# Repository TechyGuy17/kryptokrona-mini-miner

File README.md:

** THE HARDWARE IS CURRENTLY NOT TESTED **

# Kryptokrona mini miner
A bare minimum miner with a Cortex-A53 Allwinner H616 SoC made with KiCad

## Overview
A simple as possible SBC for mining kryptokrona (XKR), based on [Kononenko-K's h616 devboard](https://github.com/Kononenko-K/Allwinner_H616_Devboard/)

## [Hardware](Hardware)

The board features 64-bit 1.5GHz Quad-Core Cortex-A53 Allwinner H616 SOC, up to 8 Gbit (1 GB) of FBGA-96 16x DDR3 RAM, Micro SD slot, USB HS Host connector and integrated CP2102 USB-UART converter. 4 layers; 3,5/3,5 mil; 0,35/0,15 via, 80u prepreg.
There are [KiCad project](/Hardware), [Gerber files](/Hardware/gerber) and [PDF](/Hardware/output.pdf) avaliable.

## Software
** NOT TESTED SOFTWARE, IT COMPILES BUT MIGHT NOT ACTUALLY WORK ** 
Due to the switch to the more accessable AXP313a, the project is no longer fully compatible with the Orange Pi zero 2- But there is a workaround!

For this guide we will be using armbian, since its lightweight and has support for our processor.

The recommended OS to run this in is Ubuntu 22.04

start by downloading this repo to get the necessary files

```git clone https://github.com/TechyGuy17/kryptokrona-mini-miner```

After that we want to download the "Armbian Builder"

```git clone https://github.com/armbian/build && cd build```

Now we will do a dry run of the builder to let it download all the sources and also fix the file structure

```./compile.sh build BOARD=orangepizero2 BRANCH=current BUILD_DESKTOP=no BUILD_MINIMAL=yes KERNEL_CONFIGURE=no RELEASE=bookworm```

Now we are ready to start doing the patching. If you havent moved around the folders you can use theese commands to do the whole process

```mkdir userpatches/kernel/archive/sunxi-6.6```

```cp ../kryptokrona-mini-miner/Patches/updated-tp-axp313a.patch userpatches/kernel/archive/sunxi-6.6 ```

```cp ../kryptokrona-mini-miner/Patches/updated-tp-axp313a-uboot.patch userpatches/u-boot/u-boot-sunxi```

What this does is move in a few files that make it so we switch out everything regarding the AXP305 to 313a

Now we are ready to build for real!

```./compile.sh build BOARD=orangepizero2 BRANCH=current BUILD_DESKTOP=no BUILD_MINIMAL=yes KERNEL_CONFIGURE=no RELEASE=bookworm```

After this, you should have an image ready to be flashed to a SD card and then ready to be booted! Plug in an wifi/ethernet adapter in the board and a USB-c cable from your computer to the miner and then it should light up! The board will show up as a serial device and can be accessed through software like puTTY or minicom. settings are 115200,8,1 meaning 115200 baud rate, 8 bits and one stop bit.

# Bonus
If you want XKRig (XMRig) preinstalled to your keep on reading!

Run the following command to move the required script to the right folder 
```mv ../kryptokrona-mini-miner/Patches/customize-image.sh userpatches```

When this is in place, rerun the compile 

```./compile.sh build BOARD=orangepizero2 BRANCH=current BUILD_DESKTOP=no BUILD_MINIMAL=yes KERNEL_CONFIGURE=no RELEASE=bookworm```

This will go a lot faster since most the code is cached by now

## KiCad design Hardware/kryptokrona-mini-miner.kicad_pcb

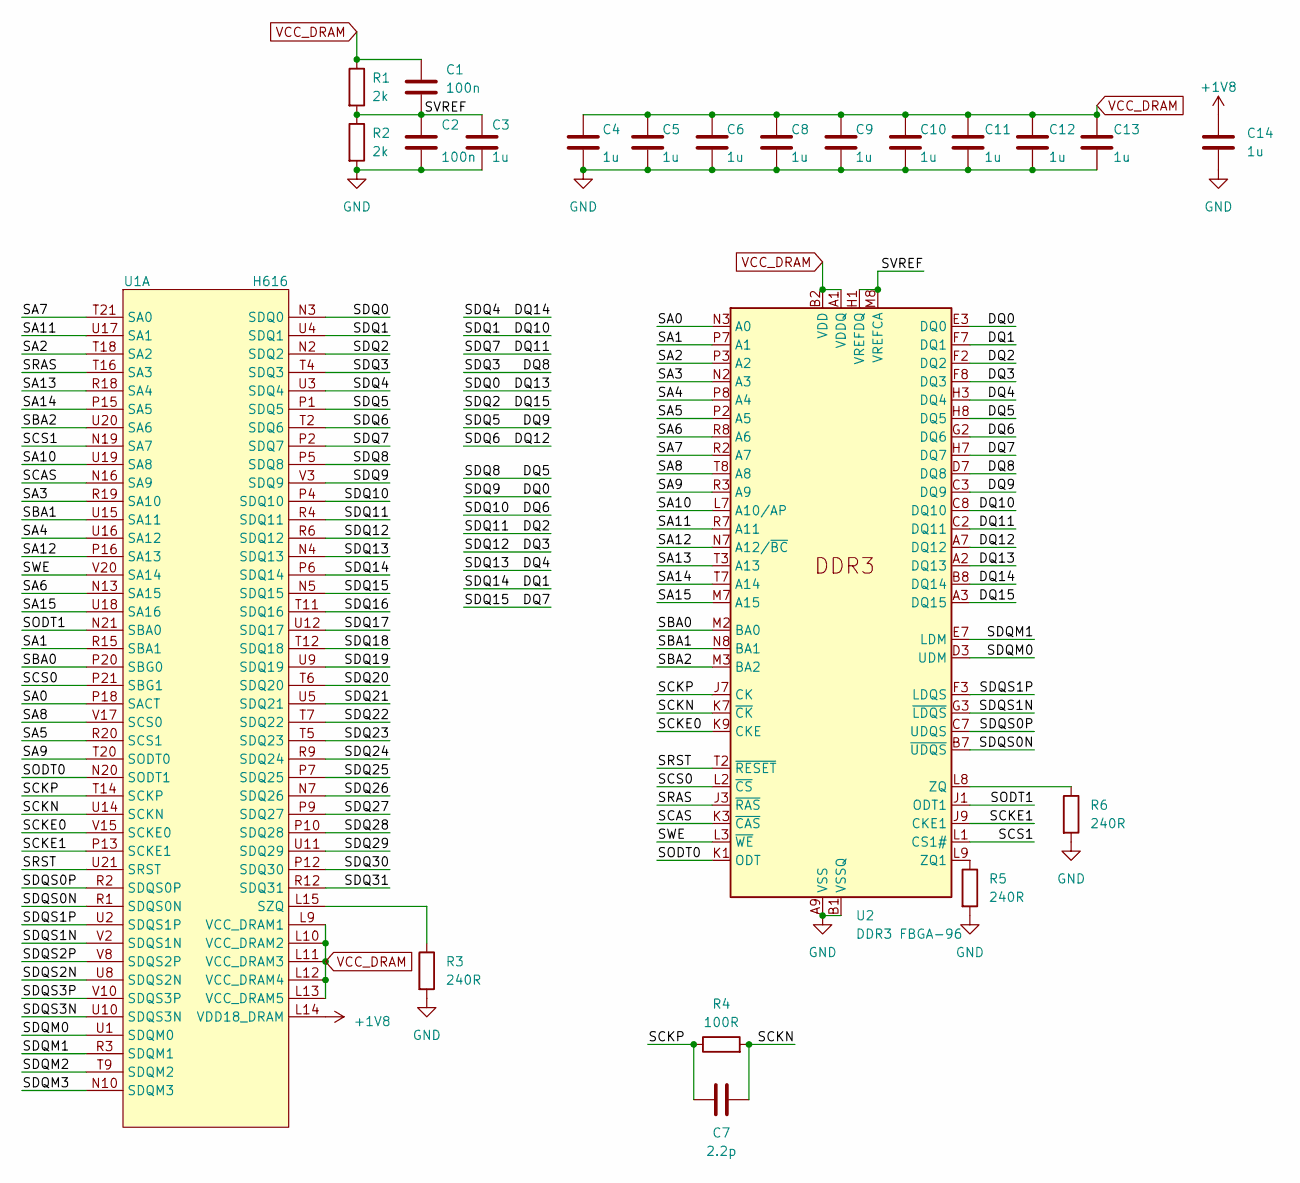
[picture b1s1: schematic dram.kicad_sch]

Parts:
C1, C2: 100n; C_0402_1005Metric_Pad0.74x0.62mm_HandSolder
C3, C4, C5, C6, C8, C9, C10, C11, C12, C13, C14: 1u; C_0402_1005Metric_Pad0.74x0.62mm_HandSolder
C7: 2.2p; C_0402_1005Metric_Pad0.74x0.62mm_HandSolder
R1, R2: 2k; R_0402_1005Metric_Pad0.72x0.64mm_HandSolder
R3, R5, R6: 240R; R_0402_1005Metric_Pad0.72x0.64mm_HandSolder
R4: 100R; R_0402_1005Metric_Pad0.72x0.64mm_HandSolder
U1: H616; H616_TFBGA284
U2: DDR3 FBGA-96; BGA-96_9.0x13.0mm_Layout2x3x16_P0.8mm

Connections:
+1V8: C14.1, U1.L14 (VDD18_DRAM); also elsewhere on the board
/DRAM/DQ0: U1.V3 (SDQ9), U2.E3 (DQ0)
/DRAM/DQ1: U1.P6 (SDQ14), U2.F7 (DQ1)
/DRAM/DQ2: U1.R4 (SDQ11), U2.F2 (DQ2)
/DRAM/DQ3: U1.R6 (SDQ12), U2.F8 (DQ3)
/DRAM/DQ4: U1.N4 (SDQ13), U2.H3 (DQ4)
/DRAM/DQ5: U1.P5 (SDQ8), U2.H8 (DQ5)
/DRAM/DQ6: U1.P4 (SDQ10), U2.G2 (DQ6)
/DRAM/DQ7: U1.N5 (SDQ15), U2.H7 (DQ7)
/DRAM/DQ8: U1.T4 (SDQ3), U2.D7 (DQ8)
/DRAM/DQ9: U1.P1 (SDQ5), U2.C3 (DQ9)
/DRAM/DQ10: U1.U4 (SDQ1), U2.C8 (DQ10)
/DRAM/DQ11: U1.P2 (SDQ7), U2.C2 (DQ11)
/DRAM/DQ12: U1.T2 (SDQ6), U2.A7 (DQ12)
/DRAM/DQ13: U1.N3 (SDQ0), U2.A2 (DQ13)
/DRAM/DQ14: U1.U3 (SDQ4), U2.B8 (DQ14)
/DRAM/DQ15: U1.N2 (SDQ2), U2.A3 (DQ15)
/DRAM/SA0: U1.P18 (SACT), U2.N3 (A0)
/DRAM/SA1: U1.R15 (SBA1), U2.P7 (A1)
/DRAM/SA2: U1.T18 (SA2), U2.P3 (A2)
/DRAM/SA3: U1.R19 (SA10), U2.N2 (A3)
/DRAM/SA4: U1.U16 (SA12), U2.P8 (A4)
/DRAM/SA5: U1.R20 (SCS1), U2.P2 (A5)
/DRAM/SA6: U1.N13 (SA15), U2.R8 (A6)
/DRAM/SA7: U1.T21 (SA0), U2.R2 (A7)
/DRAM/SA8: U1.V17 (SCS0), U2.T8 (A8)
/DRAM/SA9: U1.T20 (SODT0), U2.R3 (A9)
/DRAM/SA10: U1.U19 (SA8), U2.L7 (A10/AP)
/DRAM/SA11: U1.U17 (SA1), U2.R7 (A11)
/DRAM/SA12: U1.P16 (SA13), U2.N7 (A12/~BC)
/DRAM/SA13: U1.R18 (SA4), U2.T3 (A13)
/DRAM/SA14: U1.P15 (SA5), U2.T7 (A14)
/DRAM/SA15: U1.U18 (SA16), U2.M7 (A15)
/DRAM/SBA0: U1.P20 (SBG0), U2.M2 (BA0)
/DRAM/SBA1: U1.U15 (SA11), U2.N8 (BA1)
/DRAM/SBA2: U1.U20 (SA6), U2.M3 (BA2)
/DRAM/SCAS: U1.N16 (SA9), U2.K3 (~CAS)
/DRAM/SCKE0: U1.V15 (SCKE0), U2.K9 (CKE)
/DRAM/SCKE1: U1.P13 (SCKE1), U2.J9 (CKE1)
/DRAM/SCKN: C7.2, R4.2, U1.U14 (SCKN), U2.K7 (~CK)
/DRAM/SCKP: C7.1, R4.1, U1.T14 (SCKP), U2.J7 (CK)
/DRAM/SCS0: U1.P21 (SBG1), U2.L2 (~CS)
/DRAM/SCS1: U1.N19 (SA7), U2.L1 (CS1#)
/DRAM/SDQ16: U1.T11 (SDQ16)
/DRAM/SDQ17: U1.U12 (SDQ17)
/DRAM/SDQ18: U1.T12 (SDQ18)
/DRAM/SDQ19: U1.U9 (SDQ19)
/DRAM/SDQ20: U1.T6 (SDQ20)
/DRAM/SDQ21: U1.U5 (SDQ21)
/DRAM/SDQ22: U1.T7 (SDQ22)
/DRAM/SDQ23: U1.T5 (SDQ23)
/DRAM/SDQ24: U1.R9 (SDQ24)
/DRAM/SDQ25: U1.P7 (SDQ25)
/DRAM/SDQ26: U1.N7 (SDQ26)
/DRAM/SDQ27: U1.P9 (SDQ27)
/DRAM/SDQ28: U1.P10 (SDQ28)
/DRAM/SDQ29: U1.U11 (SDQ29)
/DRAM/SDQ30: U1.P12 (SDQ30)
/DRAM/SDQ31: U1.R12 (SDQ31)
/DRAM/SDQM0: U1.U1 (SDQM0), U2.D3 (UDM)
/DRAM/SDQM1: U1.R3 (SDQM1), U2.E7 (LDM)
/DRAM/SDQM2: U1.T9 (SDQM2)
/DRAM/SDQM3: U1.N10 (SDQM3)
/DRAM/SDQS0N: U1.R1 (SDQS0N), U2.B7 (~UDQS)
/DRAM/SDQS0P: U1.R2 (SDQS0P), U2.C7 (UDQS)
/DRAM/SDQS1N: U1.V2 (SDQS1N), U2.G3 (~LDQS)
/DRAM/SDQS1P: U1.U2 (SDQS1P), U2.F3 (LDQS)
/DRAM/SDQS2N: U1.U8 (SDQS2N)
/DRAM/SDQS2P: U1.V8 (SDQS2P)
/DRAM/SDQS3N: U1.U10 (SDQS3N)
/DRAM/SDQS3P: U1.V10 (SDQS3P)
/DRAM/SODT0: U1.N20 (SODT1), U2.K1 (ODT)
/DRAM/SODT1: U1.N21 (SBA0), U2.J1 (ODT1)
/DRAM/SRAS: U1.T16 (SA3), U2.J3 (~RAS)
/DRAM/SRST: U1.U21 (SRST), U2.T2 (~RESET)
/DRAM/SVREF: C1.2, C2.1, C3.1, R1.2, R2.1, U2.H1 (VREFDQ), U2.M8 (VREFCA)
/DRAM/SWE: U1.V20 (SA14), U2.L3 (~WE)
GND: C2.2, C3.2, C4.2, C5.2, C6.2, C8.2, C9.2, C10.2, C11.2, C12.2, C13.2, C14.2, R2.2, R3.2, R5.2, R6.2, U2.A9 (VSS), U2.B1 (VSSQ), U2.B3 (VSS), U2.B9 (VSSQ), U2.D1 (VSSQ), U2.D8 (VSSQ), U2.E1 (VSS), U2.E2 (VSSQ), U2.E8 (VSSQ), U2.F9 (VSSQ), U2.G1 (VSSQ), U2.G8 (VSS), U2.G9 (VSSQ), U2.J2 (VSS), U2.J8 (VSS), U2.M1 (VSS), U2.M9 (VSS), U2.P1 (VSS), U2.P9 (VSS), U2.T1 (VSS), U2.T9 (VSS); also elsewhere on the board
unnamed: R3.1, U1.L15 (SZQ)
unnamed: R5.1, U2.L9 (ZQ1)
unnamed: R6.1, U2.L8 (ZQ)
VCC_DRAM: C1.1, C4.1, C5.1, C6.1, C8.1, C9.1, C10.1, C11.1, C12.1, C13.1, R1.1, U1.L9 (VCC_DRAM1), U1.L10 (VCC_DRAM2), U1.L11 (VCC_DRAM3), U1.L12 (VCC_DRAM4), U1.L13 (VCC_DRAM5), U2.A1 (VDDQ), U2.A8 (VDDQ), U2.B2 (VDD), U2.C1 (VDDQ), U2.C9 (VDDQ), U2.D2 (VDDQ), U2.D9 (VDD), U2.E9 (VDDQ), U2.F1 (VDDQ), U2.G7 (VDD), U2.H2 (VDDQ), U2.H9 (VDDQ), U2.K2 (VDD), U2.K8 (VDD), U2.N1 (VDD), U2.N9 (VDD), U2.R1 (VDD), U2.R9 (VDD); also elsewhere on the board

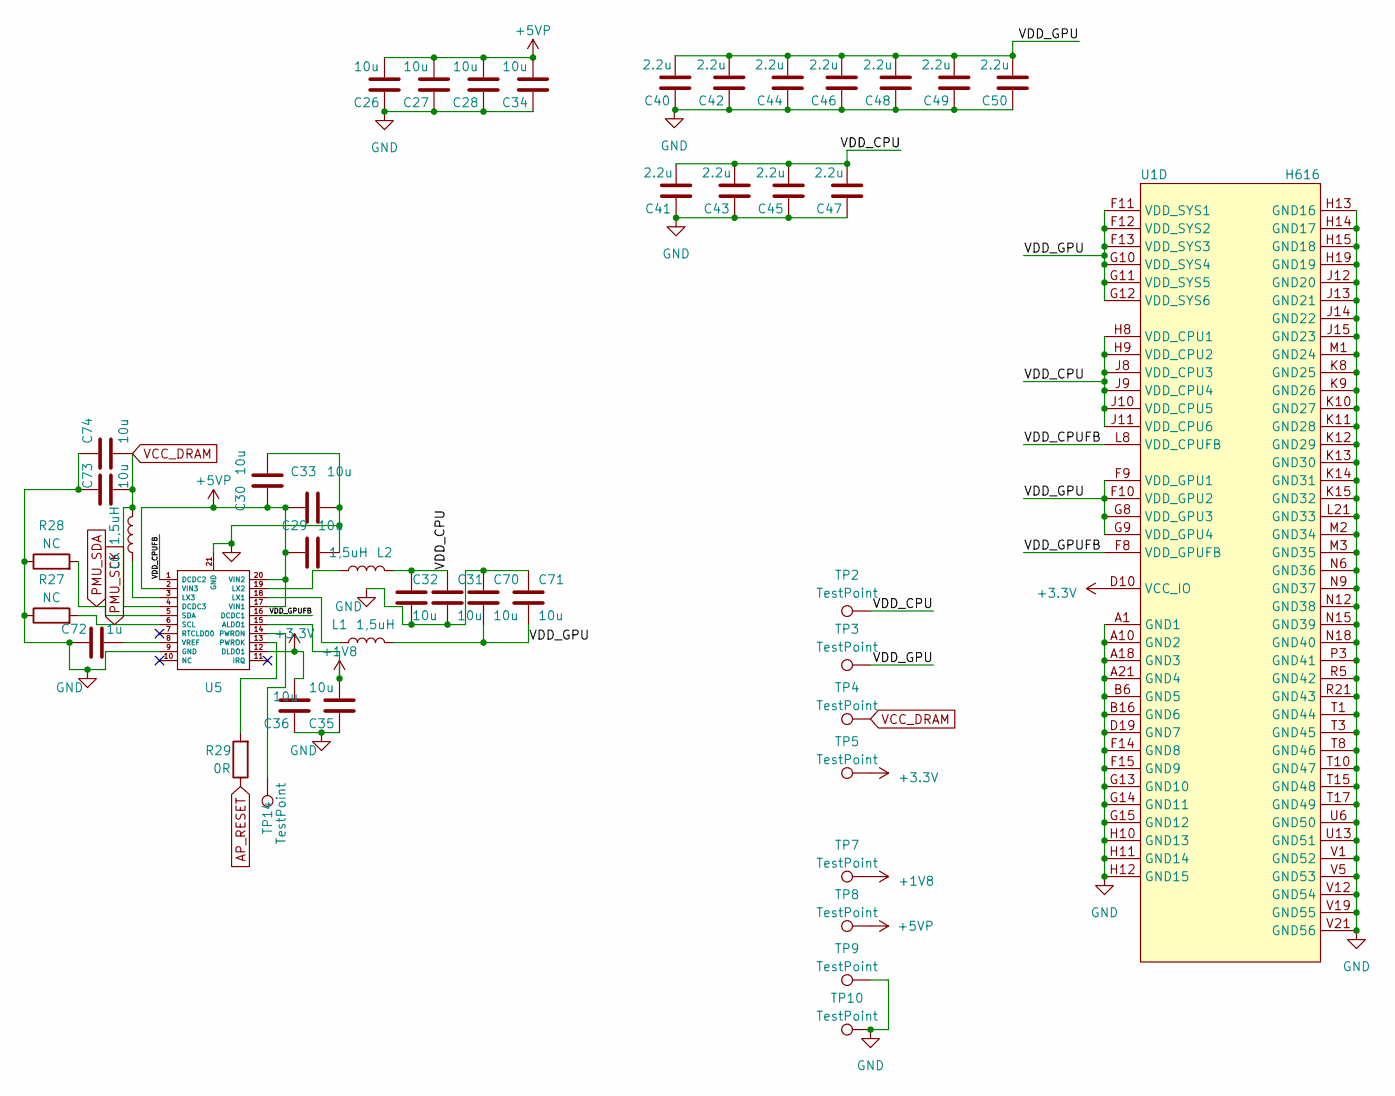
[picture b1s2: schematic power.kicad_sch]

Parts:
C26, C27, C28, C29, C30, C31, C32, C33, C34, C35, C36, C70, C71, C73, C74: 10u; C_0402_1005Metric_Pad0.74x0.62mm_HandSolder
C40, C41, C42, C43, C44, C45, C46, C47, C48, C49, C50: 2.2u; C_0402_1005Metric_Pad0.74x0.62mm_HandSolder
C72: 1u; C_0402_1005Metric_Pad0.74x0.62mm_HandSolder
L1, L2, L6: 1,5uH; L_Changjiang_FNR252010S
R27, R28: NC; R_0402_1005Metric_Pad0.72x0.64mm_HandSolder
R29: 0R; R_0402_1005Metric_Pad0.72x0.64mm_HandSolder
TP2, TP3, TP4, TP5, TP7, TP8, TP9, TP10, TP14: TestPoint; TestPoint_THTPad_D1.0mm_Drill0.5mm
U1: H616; H616_TFBGA284
U5: QFN-20-1EP_3x3mm_P0.4mm_EP1.65x1.65mm_ThermalVias

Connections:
+1V8: C35.2, TP7.1, U5.15 (ALDO1); also elsewhere on the board
+3.3V: C36.2, TP5.1, U1.D10 (VCC_IO), U5.12 (DLDO1); also elsewhere on the board
+5VP: C26.2, C27.2, C28.2, C29.1, C30.1, C33.1, C34.2, TP8.1, U5.2 (VIN3), U5.17 (VIN1), U5.20 (VIN2); also elsewhere on the board
/POWER/VDD_CPU: C31.1, C32.1, C41.2, C43.2, C45.2, C47.2, L2.1, TP2.1, U1.H8 (VDD_CPU1), U1.H9 (VDD_CPU2), U1.J8 (VDD_CPU3), U1.J9 (VDD_CPU4), U1.J10 (VDD_CPU5), U1.J11 (VDD_CPU6)
/POWER/VDD_CPUFB: U1.L8 (VDD_CPUFB), U5.1 (DCDC2)
/POWER/VDD_GPU: C40.2, C42.2, C44.2, C46.2, C48.2, C49.2, C50.2, C70.2, C71.2, L1.2, TP3.1, U1.F9 (VDD_GPU1), U1.F10 (VDD_GPU2), U1.F11 (VDD_SYS1), U1.F12 (VDD_SYS2), U1.F13 (VDD_SYS3), U1.G8 (VDD_GPU3), U1.G9 (VDD_GPU4), U1.G10 (VDD_SYS4), U1.G11 (VDD_SYS5), U1.G12 (VDD_SYS6)
/POWER/VDD_GPUFB: U1.F8 (VDD_GPUFB), U5.16 (DCDC1)
AP_RESET: R29.1; also elsewhere on the board
GND: C26.1, C27.1, C28.1, C29.2, C30.2, C31.2, C32.2, C33.2, C34.1, C35.1, C36.1, C40.1, C41.1, C42.1, C43.1, C44.1, C45.1, C46.1, C47.1, C48.1, C49.1, C50.1, C70.1, C71.1, C72.1, C73.1, C74.1, R27.1, R28.1, TP9.1, TP10.1, U1.A1 (GND1), U1.A10 (GND2), U1.A18 (GND3), U1.A21 (GND4), U1.B6 (GND5), U1.B16 (GND6), U1.D19 (GND7), U1.F14 (GND8), U1.F15 (GND9), U1.G13 (GND10), U1.G14 (GND11), U1.G15 (GND12), U1.H10 (GND13), U1.H11 (GND14), U1.H12 (GND15), U1.H13 (GND16), U1.H14 (GND17), U1.H15 (GND18), U1.H19 (GND19), U1.J12 (GND20), U1.J13 (GND21), U1.J14 (GND22), U1.J15 (GND23), U1.K8 (GND25), U1.K9 (GND26), U1.K10 (GND27), U1.K11 (GND28), U1.K12 (GND29), U1.K13 (GND30), U1.K14 (GND31), U1.K15 (GND32), U1.L21 (GND33), U1.M1 (GND24), U1.M2 (GND34), U1.M3 (GND35), U1.N6 (GND36), U1.N9 (GND37), U1.N12 (GND38), U1.N15 (GND39), U1.N18 (GND40), U1.P3 (GND41), U1.R5 (GND42), U1.R21 (GND43), U1.T1 (GND44), U1.T3 (GND45), U1.T8 (GND46), U1.T10 (GND47), U1.T15 (GND48), U1.T17 (GND49), U1.U6 (GND50), U1.U13 (GND51), U1.V1 (GND52), U1.V5 (GND53), U1.V12 (GND54), U1.V19 (GND55), U1.V21 (GND56), U5.9 (GND), U5.21 (GND); also elsewhere on the board
unnamed: L1.1, U5.18 (LX1)
unnamed: L2.2, U5.19 (LX2)
unnamed: L6.1, U5.3 (LX3)
unnamed: R29.2, U5.13 (PWROK)
unnamed: TP14.1, U5.14 (PWRON)
unnamed: C72.2, U5.8 (VREF)
PMU_SCK: R27.2, U5.6 (SCL); also elsewhere on the board
PMU_SDA: R28.2, U5.5 (SDA); also elsewhere on the board
VCC_DRAM: C73.2, C74.2, L6.2, TP4.1, U5.4 (DCDC3); also elsewhere on the board

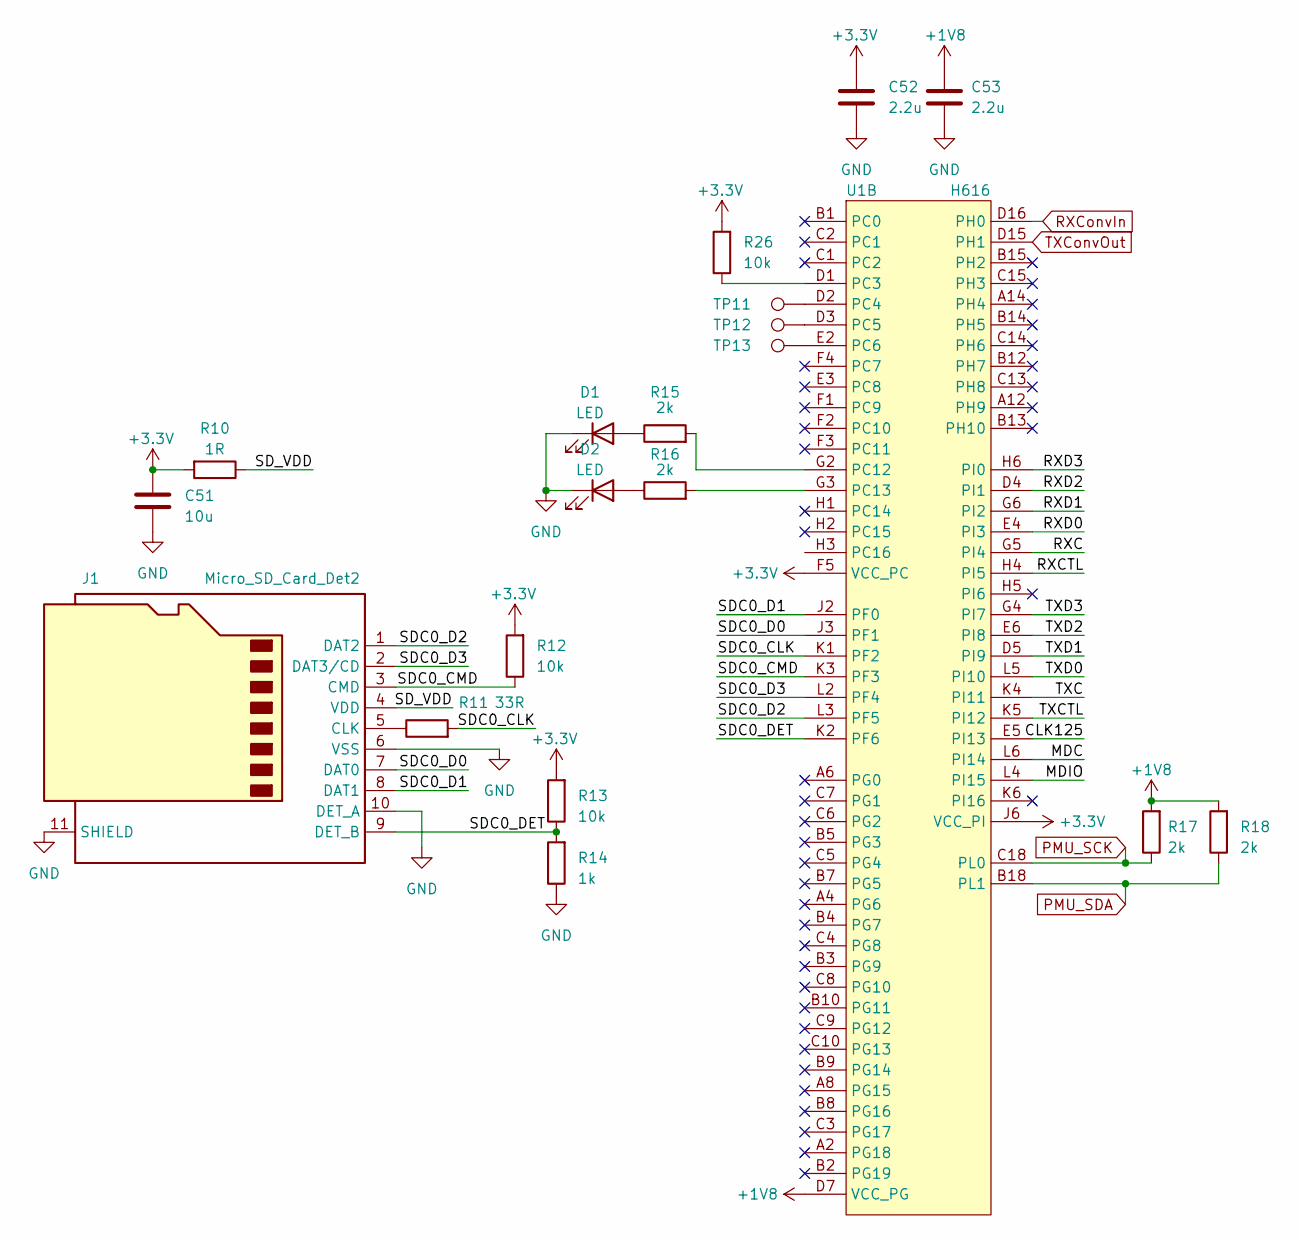
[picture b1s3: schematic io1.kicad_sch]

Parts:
C51: 10u; C_0402_1005Metric_Pad0.74x0.62mm_HandSolder
C52, C53: 2.2u; C_0402_1005Metric_Pad0.74x0.62mm_HandSolder
D1, D2: LED; LED_0603_1608Metric_Pad1.05x0.95mm_HandSolder
J1: Micro_SD_Card_Det2; microSD_HC_Hirose_DM3AT-SF-PEJM5
R10: 1R; R_0402_1005Metric_Pad0.72x0.64mm_HandSolder
R11: 33R; R_0402_1005Metric_Pad0.72x0.64mm_HandSolder
R12, R13, R26: 10k; R_0402_1005Metric_Pad0.72x0.64mm_HandSolder
R14: 1k; R_0402_1005Metric_Pad0.72x0.64mm_HandSolder
R15, R16, R17, R18: 2k; R_0402_1005Metric_Pad0.72x0.64mm_HandSolder
TP11, TP12, TP13: TestPoint; TestPoint_THTPad_D1.0mm_Drill0.5mm
U1: H616; H616_TFBGA284

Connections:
+1V8: C53.1, R17.2, R18.2, U1.D7 (VCC_PG); also elsewhere on the board
+3.3V: C51.1, C52.1, R10.2, R12.2, R13.2, R26.2, U1.F5 (VCC_PC), U1.J6 (VCC_PI); also elsewhere on the board
/IO1/CLK125: U1.E5 (PI13)
/IO1/MDC: U1.L6 (PI14)
/IO1/MDIO: U1.L4 (PI15)
/IO1/RXC: U1.G5 (PI4)
/IO1/RXCTL: U1.H4 (PI5)
/IO1/RXD0: U1.E4 (PI3)
/IO1/RXD1: U1.G6 (PI2)
/IO1/RXD2: U1.D4 (PI1)
/IO1/RXD3: U1.H6 (PI0)
/IO1/SDC0_CLK: R11.2, U1.K1 (PF2)
/IO1/SDC0_CMD: J1.3 (CMD), R12.1, U1.K3 (PF3)
/IO1/SDC0_D0: J1.7 (DAT0), U1.J3 (PF1)
/IO1/SDC0_D1: J1.8 (DAT1), U1.J2 (PF0)
/IO1/SDC0_D2: J1.1 (DAT2), U1.L3 (PF5)
/IO1/SDC0_D3: J1.2 (DAT3/CD), U1.L2 (PF4)
/IO1/SDC0_DET: J1.9 (DET_B), R13.1, R14.2, U1.K2 (PF6)
/IO1/SD_VDD: J1.4 (VDD), R10.1
/IO1/TXC: U1.K4 (PI11)
/IO1/TXCTL: U1.K5 (PI12)
/IO1/TXD0: U1.L5 (PI10)
/IO1/TXD1: U1.D5 (PI9)
/IO1/TXD2: U1.E6 (PI8)
/IO1/TXD3: U1.G4 (PI7)
GND: C51.2, C52.2, C53.2, D1.1 (K), D2.1 (K), J1.6 (VSS), J1.10 (DET_A), J1.11 (SHIELD), R14.1; also elsewhere on the board
unnamed: D1.2 (A), R15.1
unnamed: D2.2 (A), R16.1
unnamed: J1.5 (CLK), R11.1
unnamed: R26.1, U1.D1 (PC3)
unnamed: TP11.1, U1.D2 (PC4)
unnamed: TP12.1, U1.D3 (PC5)
unnamed: TP13.1, U1.E2 (PC6)
unnamed: R15.2, U1.G2 (PC12)
unnamed: R16.2, U1.G3 (PC13)
PMU_SCK: R17.1, U1.C18 (PL0); also elsewhere on the board
PMU_SDA: R18.1, U1.B18 (PL1); also elsewhere on the board
RXConvIn: U1.D16 (PH0); also elsewhere on the board
TXConvOut: U1.D15 (PH1); also elsewhere on the board

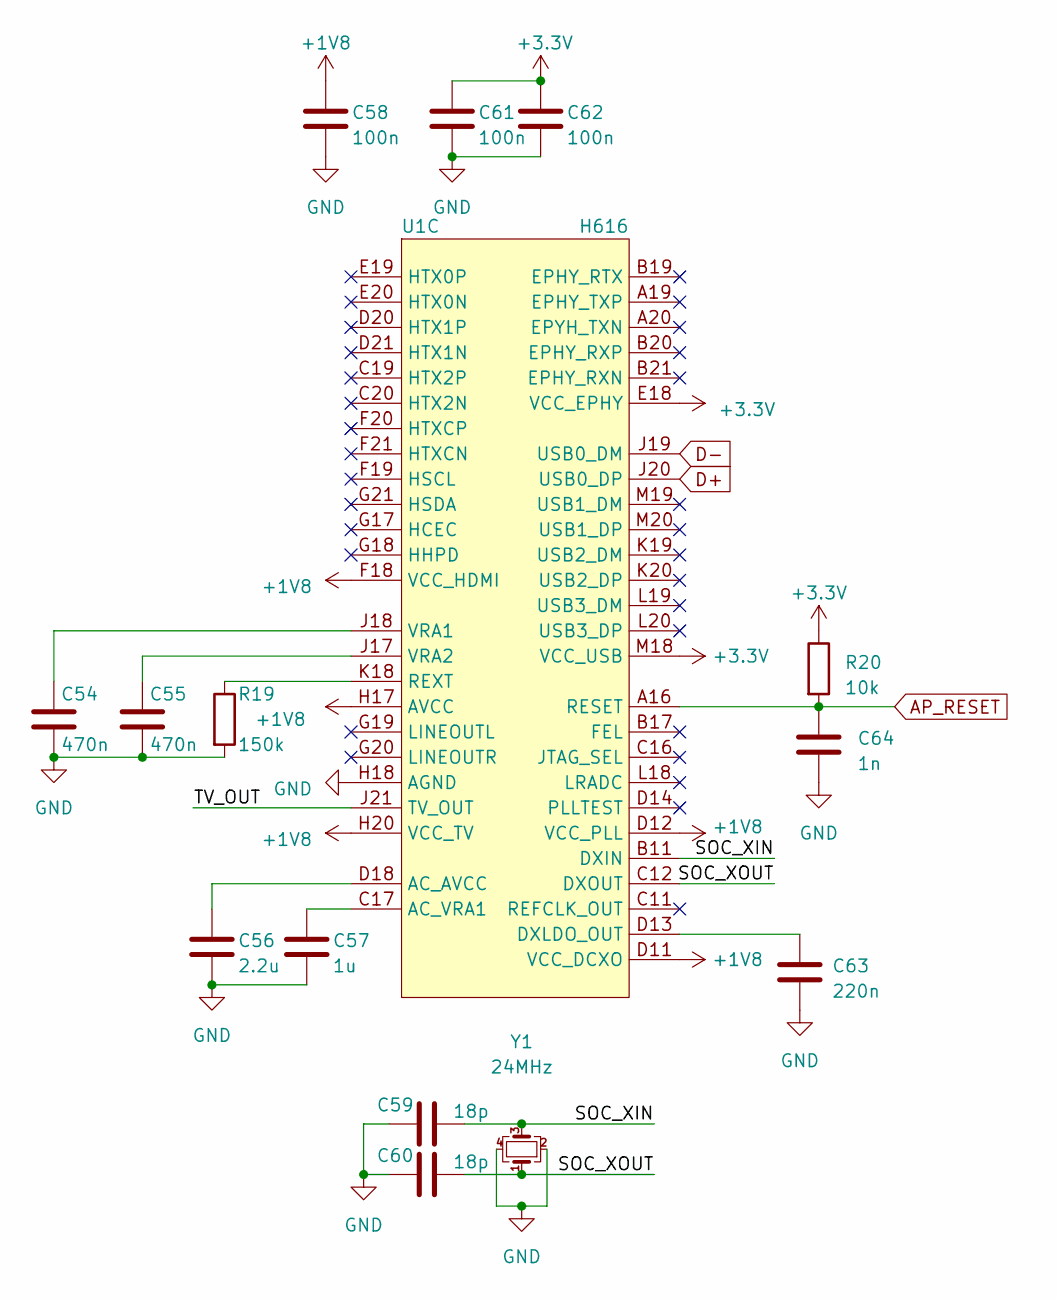
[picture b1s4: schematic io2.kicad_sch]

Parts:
C54, C55: 470n; C_0402_1005Metric_Pad0.74x0.62mm_HandSolder
C56: 2.2u; C_0402_1005Metric_Pad0.74x0.62mm_HandSolder
C57: 1u; C_0402_1005Metric_Pad0.74x0.62mm_HandSolder
C58, C61, C62: 100n; C_0402_1005Metric_Pad0.74x0.62mm_HandSolder
C59, C60: 18p; C_0402_1005Metric_Pad0.74x0.62mm_HandSolder
C63: 220n; C_0402_1005Metric_Pad0.74x0.62mm_HandSolder
C64: 1n; C_0402_1005Metric_Pad0.74x0.62mm_HandSolder
R19: 150k; R_0402_1005Metric_Pad0.72x0.64mm_HandSolder
R20: 10k; R_0402_1005Metric_Pad0.72x0.64mm_HandSolder
U1: H616; H616_TFBGA284
Y1: 24MHz; Crystal_SMD_2520-4Pin_2.5x2.0mm

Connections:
+1V8: C58.1, U1.D11 (VCC_DCXO), U1.D12 (VCC_PLL), U1.F18 (VCC_HDMI), U1.H17 (AVCC), U1.H20 (VCC_TV); also elsewhere on the board
+3.3V: C61.1, C62.1, R20.1, U1.E18 (VCC_EPHY), U1.M18 (VCC_USB); also elsewhere on the board
/IO2/SOC_XIN: C59.2, U1.B11 (DXIN), Y1.3
/IO2/SOC_XOUT: C60.2, U1.C12 (DXOUT), Y1.1
/IO2/TV_OUT: U1.J21 (TV_OUT)
AP_RESET: C64.1, R20.2, U1.A16 (RESET); also elsewhere on the board
D+: U1.J20 (USB0_DP); also elsewhere on the board
D-: U1.J19 (USB0_DM); also elsewhere on the board
GND: C54.2, C55.2, C56.2, C57.2, C58.2, C59.1, C60.1, C61.2, C62.2, C63.2, C64.2, R19.2, U1.H18 (AGND), Y1.2, Y1.4; also elsewhere on the board
unnamed: C56.1, U1.D18 (AC_AVCC)
unnamed: C57.1, U1.C17 (AC_VRA1)
unnamed: C63.1, U1.D13 (DXLDO_OUT)
unnamed: R19.1, U1.K18 (REXT)
unnamed: C54.1, U1.J18 (VRA1)
unnamed: C55.1, U1.J17 (VRA2)

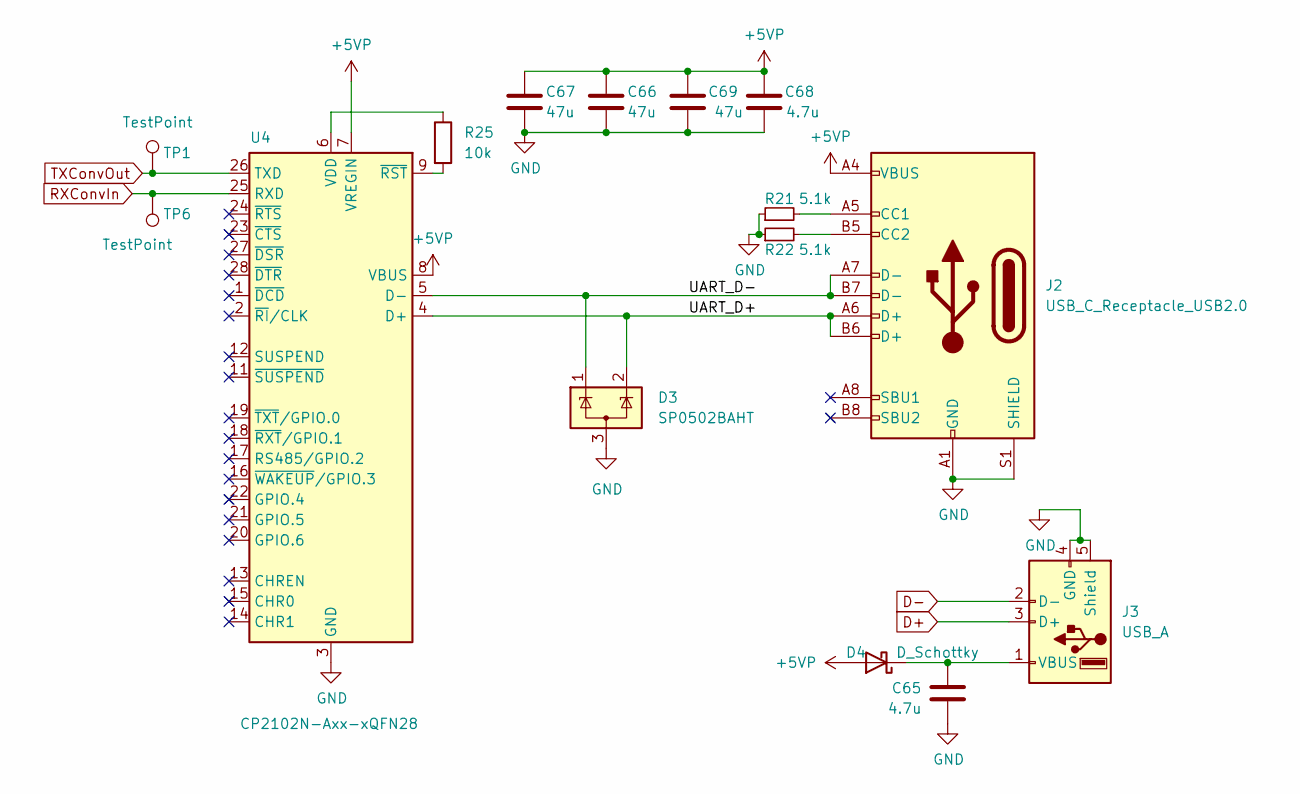
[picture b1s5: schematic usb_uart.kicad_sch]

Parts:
C65, C68: 4.7u; C_0402_1005Metric_Pad0.74x0.62mm_HandSolder
C66, C67, C69: 47u; C_1206_3216Metric_Pad1.33x1.80mm_HandSolder
D3: SP0502BAHT; SOT-23
D4: D_Schottky; D_SOD-323_HandSoldering
J2: USB_C_Receptacle_USB2.0; USB_C_Receptacle_Palconn_UTC16-G
J3: USB_A; USB_A_Molex_67643_Horizontal
R21, R22: 5.1k; R_0402_1005Metric_Pad0.72x0.64mm_HandSolder
R25: 10k; R_0402_1005Metric_Pad0.72x0.64mm_HandSolder
TP1, TP6: TestPoint; TestPoint_THTPad_D1.0mm_Drill0.5mm
U4: CP2102N-Axx-xQFN28; QFN-28-1EP_5x5mm_P0.5mm_EP3.35x3.35mm

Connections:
+5VP: C66.1, C67.1, C68.1, C69.1, D4.2 (A), J2.A4 (VBUS), J2.A9 (VBUS), J2.B4 (VBUS), J2.B9 (VBUS), U4.7 (VREGIN), U4.8 (VBUS); also elsewhere on the board
/USB-UART/UART_D+: D3.2 (K), J2.A6 (D+), J2.B6 (D+), U4.4 (D+)
/USB-UART/UART_D-: D3.1 (K), J2.A7 (D-), J2.B7 (D-), U4.5 (D-)
D+: J3.3 (D+); also elsewhere on the board
D-: J3.2 (D-); also elsewhere on the board
GND: C65.2, C66.2, C67.2, C68.2, C69.2, D3.3 (A), J2.A1 (GND), J2.A12 (GND), J2.B1 (GND), J2.B12 (GND), J2.S1 (SHIELD), J3.4 (GND), J3.5 (Shield), R21.1, R22.1, U4.3 (GND), U4.29 (GND); also elsewhere on the board
unnamed: C65.1, D4.1 (K), J3.1 (VBUS)
unnamed: J2.A5 (CC1), R21.2
unnamed: J2.B5 (CC2), R22.2
unnamed: R25.1, U4.6 (VDD)
unnamed: R25.2, U4.9 (~RST)
RXConvIn: TP6.1, U4.25 (RXD); also elsewhere on the board
TXConvOut: TP1.1, U4.26 (TXD); also elsewhere on the board

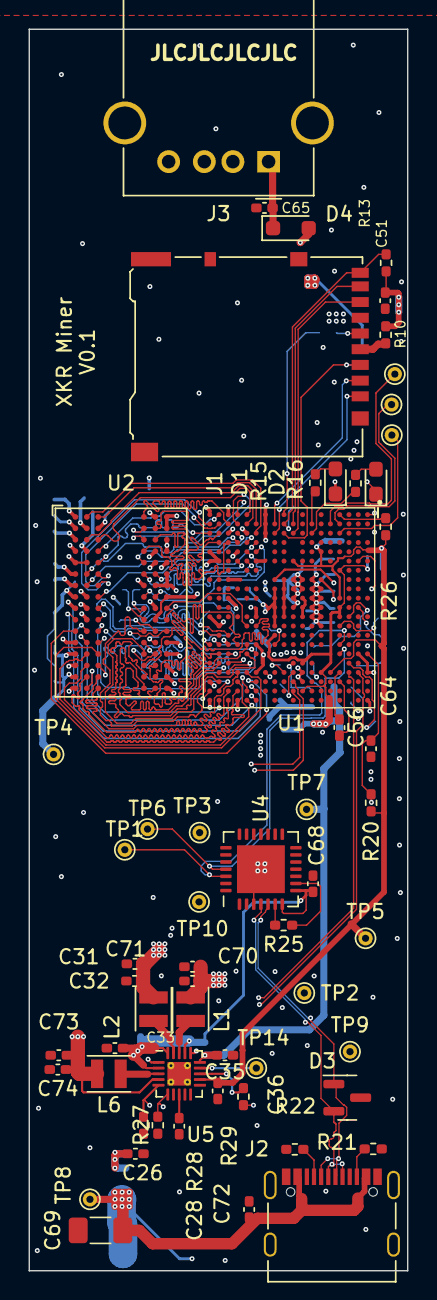
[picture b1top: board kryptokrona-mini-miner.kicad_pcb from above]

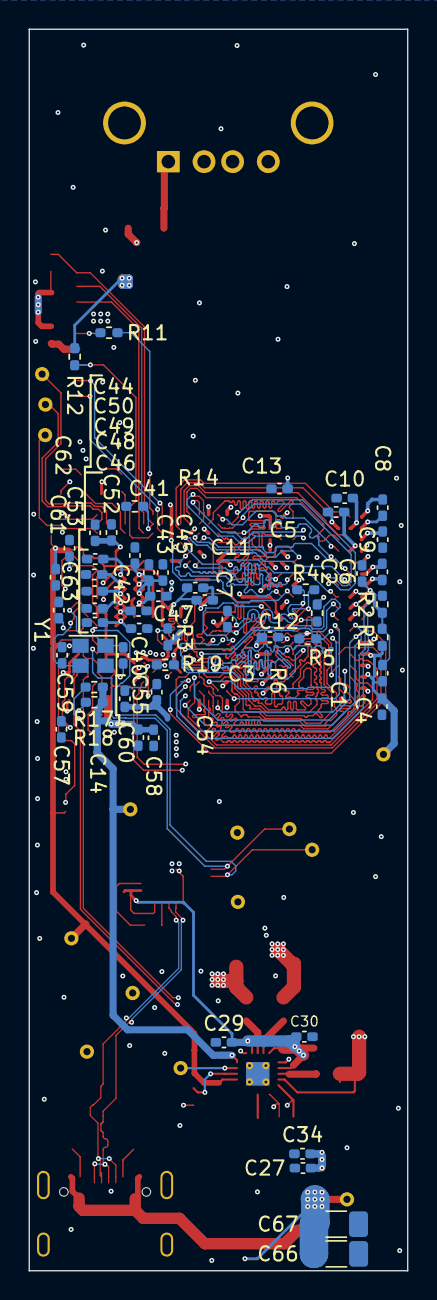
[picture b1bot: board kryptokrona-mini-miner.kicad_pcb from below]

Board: 4 copper layers, 26.5 x 86.9 mm, 113 parts (55 on the bottom side), 111 nets.

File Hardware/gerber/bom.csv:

Designator,Footprint,Quantity,Value,LCSC Part #
"C1, C2, C58, C61, C62",0402,5,100n,
"C10, C11, C12, C13, C14, C3, C4, C5, C57, C6, C72, C8, C9",0402,13,1u,
"C26, C27, C28, C29, C30, C31, C32, C33, C34, C35, C36, C51, C70, C71, C73, C74",0402,16,10u,
"C40, C41, C42, C43, C44, C45, C46, C47, C48, C49, C50, C52, C53, C56",0402,14,2.2u,
"C54, C55",0402,2,470n,
"C59, C60",0402,2,18p,
C63,0402,1,220n,
C64,0402,1,1n,
"C65, C68",0402,2,4.7u,
"C66, C67, C69",1206,3,47u,
C7,0402,1,2.2p,
"D1, D2",0603,2,LED,
D3,SOT-23,1,SP0502BAHT,
D4,D_SOD-323_HandSoldering,1,D_Schottky,
J1,microSD_HC_Hirose_DM3AT-SF-PEJM5,1,Micro_SD_Card_Det2,
J2,USB_C_Receptacle_Palconn_UTC16-G,1,USB_C_Receptacle_USB2.0,
J3,USB_A_Molex_67643_Horizontal,1,USB_A,
"L1, L2, L6",L_Changjiang_FNR252010S,3,"1,5uH",
"R1, R15, R16, R17, R18, R2",0402,6,2k,
R10,0402,1,1R,
R11,0402,1,33R,
"R12, R13, R20, R25, R26",0402,5,10k,
R14,0402,1,1k,
R19,0402,1,150k,
"R21, R22",0402,2,5.1k,
"R27, R28",0402,2,NC,
R29,0402,1,0R,
"R3, R5, R6",0402,3,240R,
R4,0402,1,100R,
"TP10, TP11, TP12, TP13, TP14, TP2, TP3, TP4, TP5, TP7, TP8, TP9",TestPoint_THTPad_D1.0mm_Drill0.5mm,12,TestPoint,
U1,H616_TFBGA284,1,H616,
U2,BGA-96_9.0x13.0mm_Layout2x3x16_P0.8mm,1,DDR3 FBGA-96,
U4,QFN-28-1EP_5x5mm_P0.5mm_EP3.35x3.35mm,1,CP2102N-Axx-xQFN28,
U5,QFN-20-1EP_3x3mm_P0.4mm_EP1.65x1.65mm_ThermalVias,1,~,
Y1,Crystal_SMD_2520-4Pin_2.5x2.0mm,1,25MHz,

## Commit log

2024-04-13 Upload of untested hardware
2024-04-13 Updated readme, deleted files
2024-04-18 added testpoint for TX/RX and updated readme
2024-04-18 Updated git ignore
2024-04-18 removed folder
2024-04-20 Added guide and patches
2024-04-20 Made it look better
2024-04-20 Made it look better, again
2024-04-20 Made the text clearer
2024-04-20 Fixed typo
2024-04-22 Added server
2024-04-23 More fields in the webpage, updated customization script
